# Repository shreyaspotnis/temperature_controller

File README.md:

# temperature_controller
A unipolar output temperature controller

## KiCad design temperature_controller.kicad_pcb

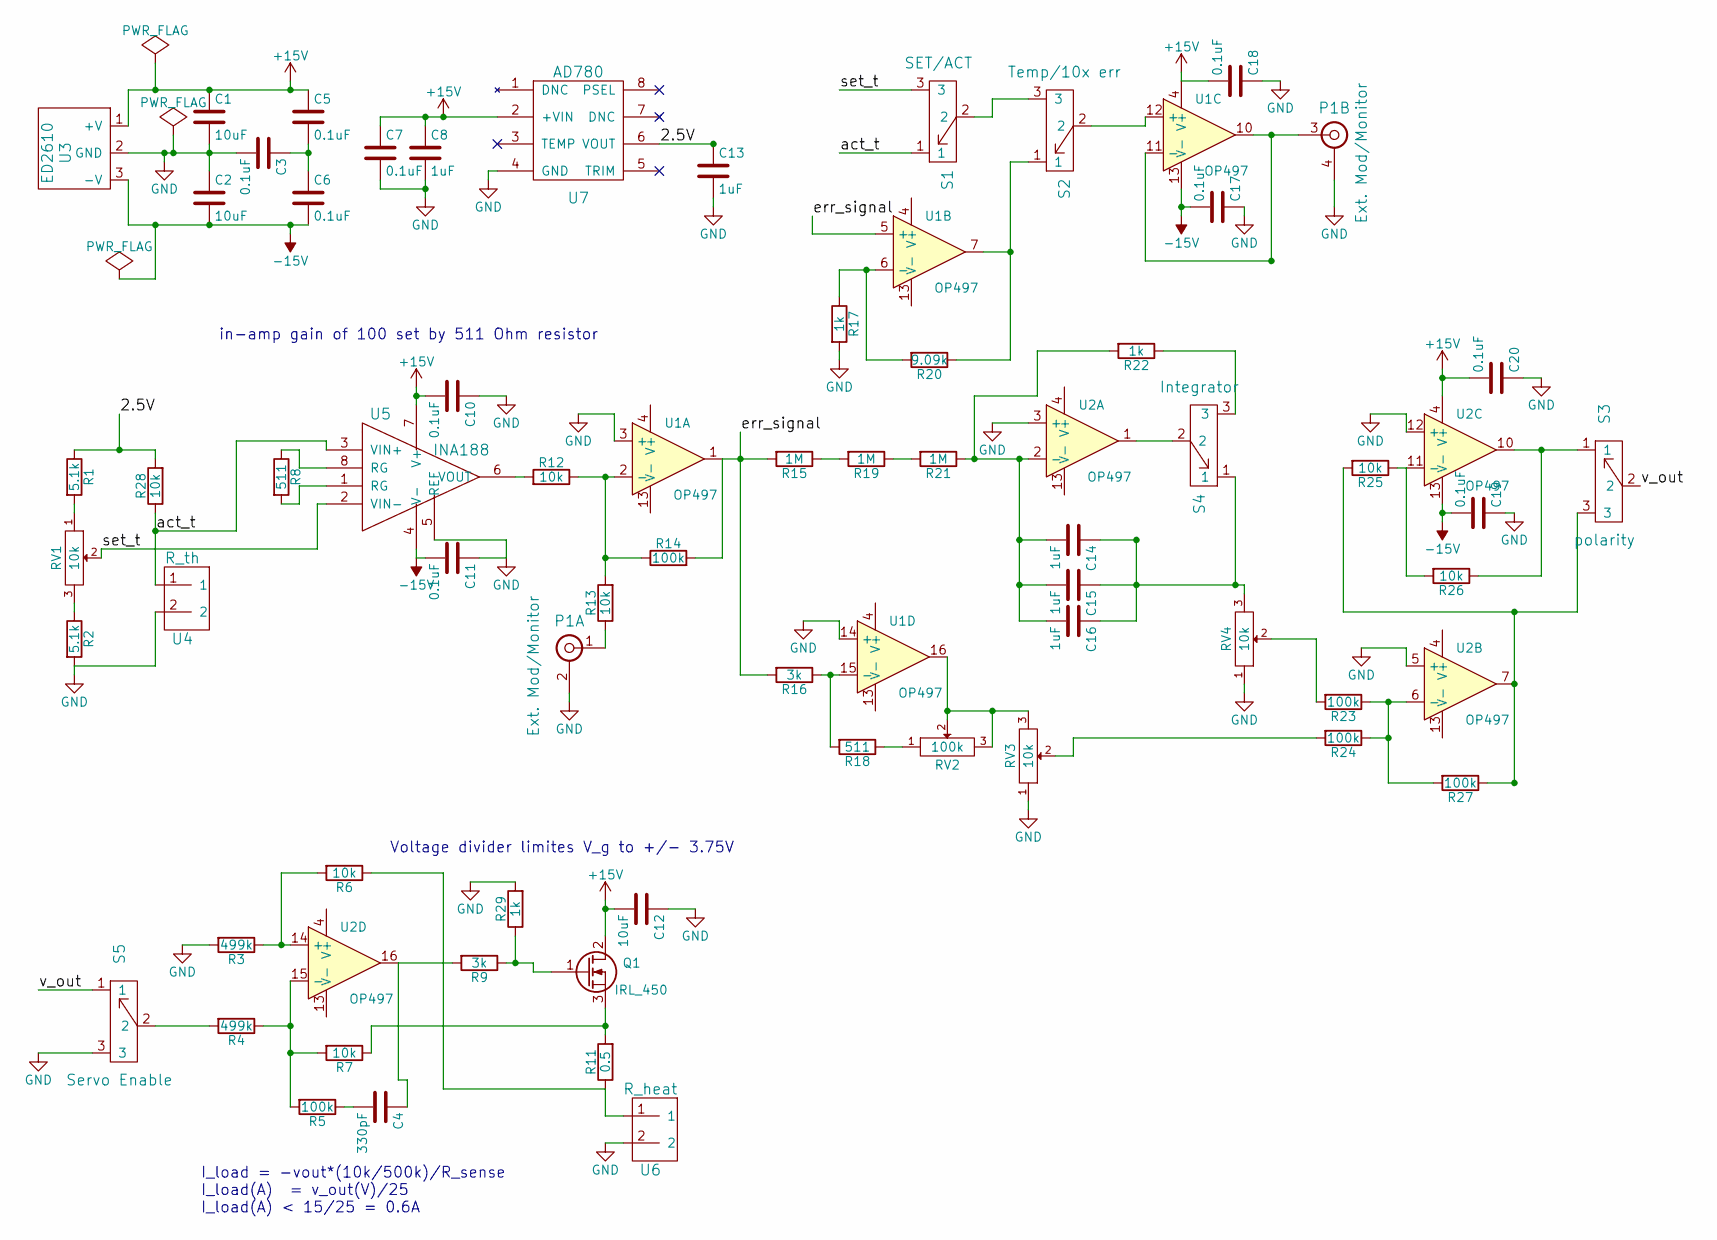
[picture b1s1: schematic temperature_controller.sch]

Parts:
C1, C2, C12: 10uF; C_0805_HandSoldering
C3, C5, C6, C7, C10, C11, C17, C18, C19, C20: 0.1uF; C_0805_HandSoldering
C4: 330pF; C_0603_HandSoldering
C8, C13, C14, C15, C16: 1uF; C_0603_HandSoldering
P1: Ext. Mod/Monitor; Dual-BNC-ARF2136
Q1: IRL_450; TO-220_Neutral123_Vertical
R1, R2: 5.1k; R_0603_HandSoldering
R3, R4: 499k; R_0603_HandSoldering
R5, R14, R23, R24, R27: 100k; R_0603_HandSoldering
R6, R7, R12, R13, R25, R26, R28: 10k; R_0603_HandSoldering
R8, R18: 511; R_0603_HandSoldering
R9: 3k; C_0603_HandSoldering
R11: 0.5; R_2512_HandSoldering
R15, R19, R21: 1M; R_0603_HandSoldering
R16: 3k; R_0603_HandSoldering
R17, R22, R29: 1k; R_0603_HandSoldering
R20: 9.09k; R_0603_HandSoldering
RV1: 10k; VishaySpectrol536
RV2: 100k; Bourns-PV36W104C01B00-trimmer
RV3, RV4: 10k; Bourns-PV36W104C01B00-trimmer
S1: SET/ACT; SPDT-Horizontal
S2: Temp/10x err; SPDT-Horizontal
S3: polarity; CJS-1200TB-SPDT
S4: Integrator; CJS-1200TB-SPDT
S5: Servo Enable; SPDT-Horizontal
U1, U2: OP497; SOIC-16W_7.5x10.3mm_Pitch1.27mm
U3: ED2610
U4: R_th; ED2580
U5: INA188; SOIC-8_3.9x4.9mm_Pitch1.27mm
U6: R_heat; ED2580
U7: AD780; SOIC-8_3.9x4.9mm_Pitch1.27mm

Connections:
+15V: C1.1, C5.1, C7.1, C8.1, C10.2, C12.2, C18.2, C20.2, Q1.2 (D), U1.4 (V+), U2.4 (V+), U3.1 (+V), U5.7 (V+), U7.2 (+VIN)
-15V: C2.2, C6.2, C11.2, C17.2, C19.2, U1.13 (V-), U2.13 (V-), U3.3 (-V), U5.4 (V-)
/2.5V: C13.1, R1.1, R28.2, U7.6 (VOUT)
/act_t: R28.1, S1.1, U4.1, U5.3 (VIN+)
/err_signal: R14.2, R15.2, R16.2, U1.1, U1.5 (+)
/set_t: RV1.2, S1.3, U5.2 (VIN-)
/v_out: S3.2, S5.1
GND: C1.2, C2.1, C3.2, C7.2, C8.2, C10.1, C11.1, C12.1, C13.2, C17.1, C18.1, C19.1, C20.1, P1.2, P1.4, R2.2, R3.2, R17.2, R29.2, RV3.1, RV4.1, S5.3, U1.3 (+), U1.14 (+), U2.3 (+), U2.5 (+), U2.12 (+), U3.2 (GND), U4.2, U5.5 (REF), U6.2, U7.4 (GND)
unnamed: C3.1, C5.2, C6.1
unnamed: C4.1, R9.2, U2.16
unnamed: C4.2, R5.1
unnamed: C14.1, C15.1, C16.1, RV4.3, S4.1
unnamed: C14.2, C15.2, C16.2, R21.1, R22.2, U2.2 (-)
unnamed: P1.1, R13.1
unnamed: P1.3, U1.10, U1.11 (-)
unnamed: Q1.1 (G), R9.1, R29.1
unnamed: Q1.3 (S), R7.1, R11.2
unnamed: R1.2, RV1.1
unnamed: R2.1, RV1.3
unnamed: R3.1, R6.2, U2.14 (+)
unnamed: R4.1, R5.2, R7.2, U2.15 (-)
unnamed: R4.2, S5.2
unnamed: R8.1, U5.8 (RG)
unnamed: R8.2, U5.1 (RG)
unnamed: R6.1, R11.1, U6.1
unnamed: R12.1, R13.2, R14.1, U1.2 (-)
unnamed: R12.2, U5.6 (VOUT)
unnamed: R15.1, R19.2
unnamed: R16.1, R18.2, U1.15 (-)
unnamed: R17.1, R20.2, U1.6 (-)
unnamed: R18.1, RV2.1
unnamed: R19.1, R21.2
unnamed: R20.1, S2.1, U1.7
unnamed: R22.1, S4.3
unnamed: R23.1, R24.1, R27.2, U2.6 (-)
unnamed: R23.2, RV4.2
unnamed: R24.2, RV3.2
unnamed: R25.1, R26.2, U2.11 (-)
unnamed: R25.2, R27.1, S3.3, U2.7
unnamed: R26.1, S3.1, U2.10
unnamed: RV2.2, RV2.3, RV3.3, U1.16
unnamed: S1.2, S2.3
unnamed: S2.2, U1.12 (+)
unnamed: S4.2, U2.1

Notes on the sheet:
in-amp gain of 100 set by 511 Ohm resistor
I_load = -vout*(10k/500k)/R_sense I_load(A) = v_out(V)/25 I_load(A) < 15/25 = 0.6A
Voltage divider limites V_g to +/- 3.75V

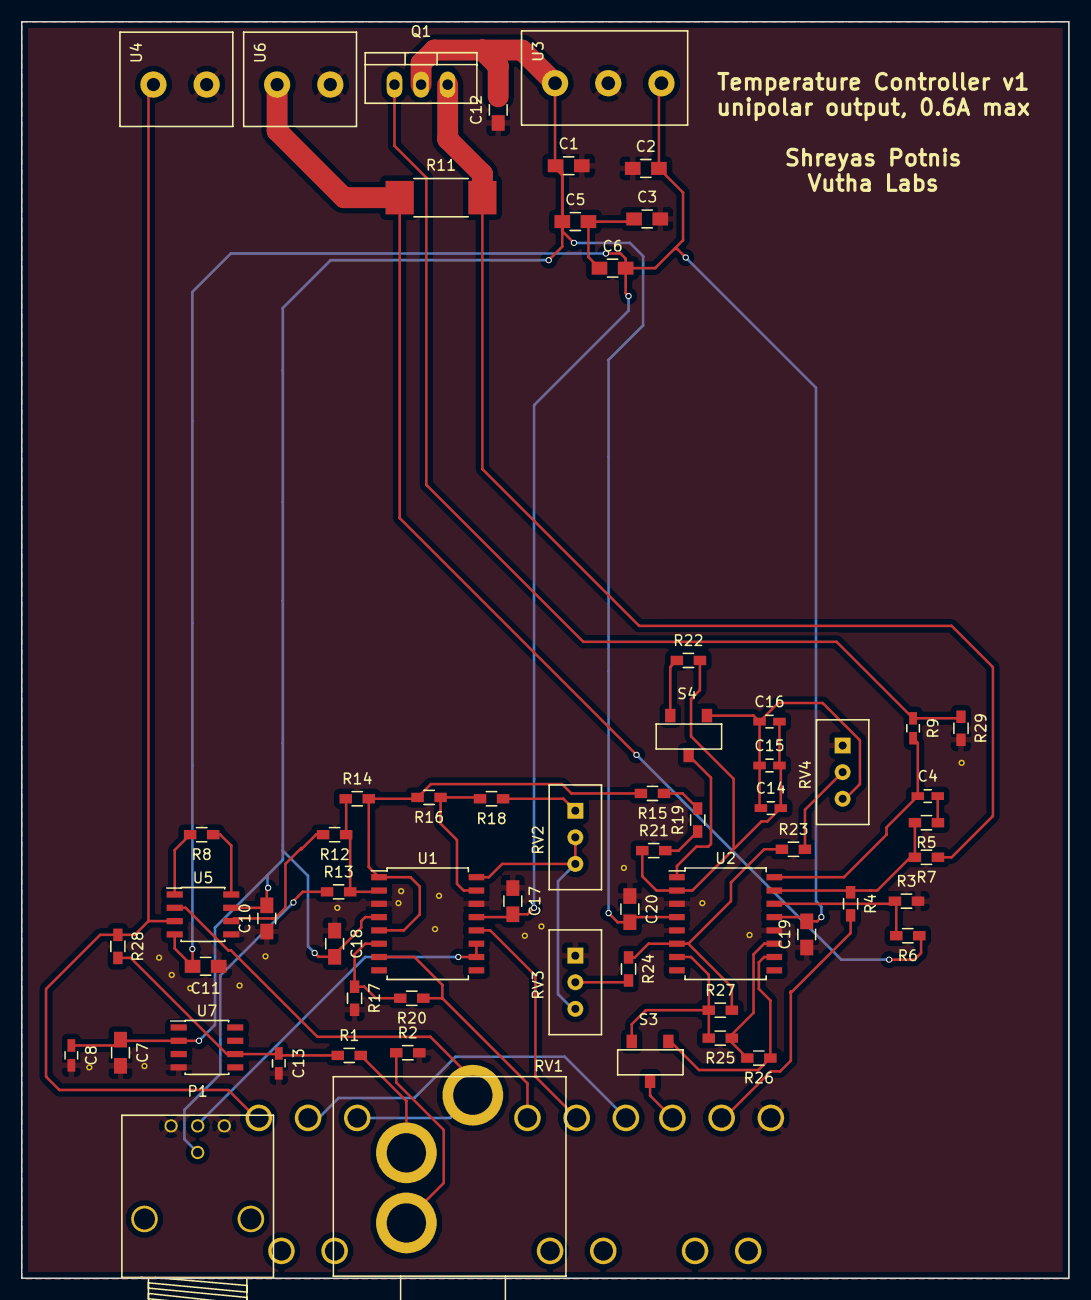
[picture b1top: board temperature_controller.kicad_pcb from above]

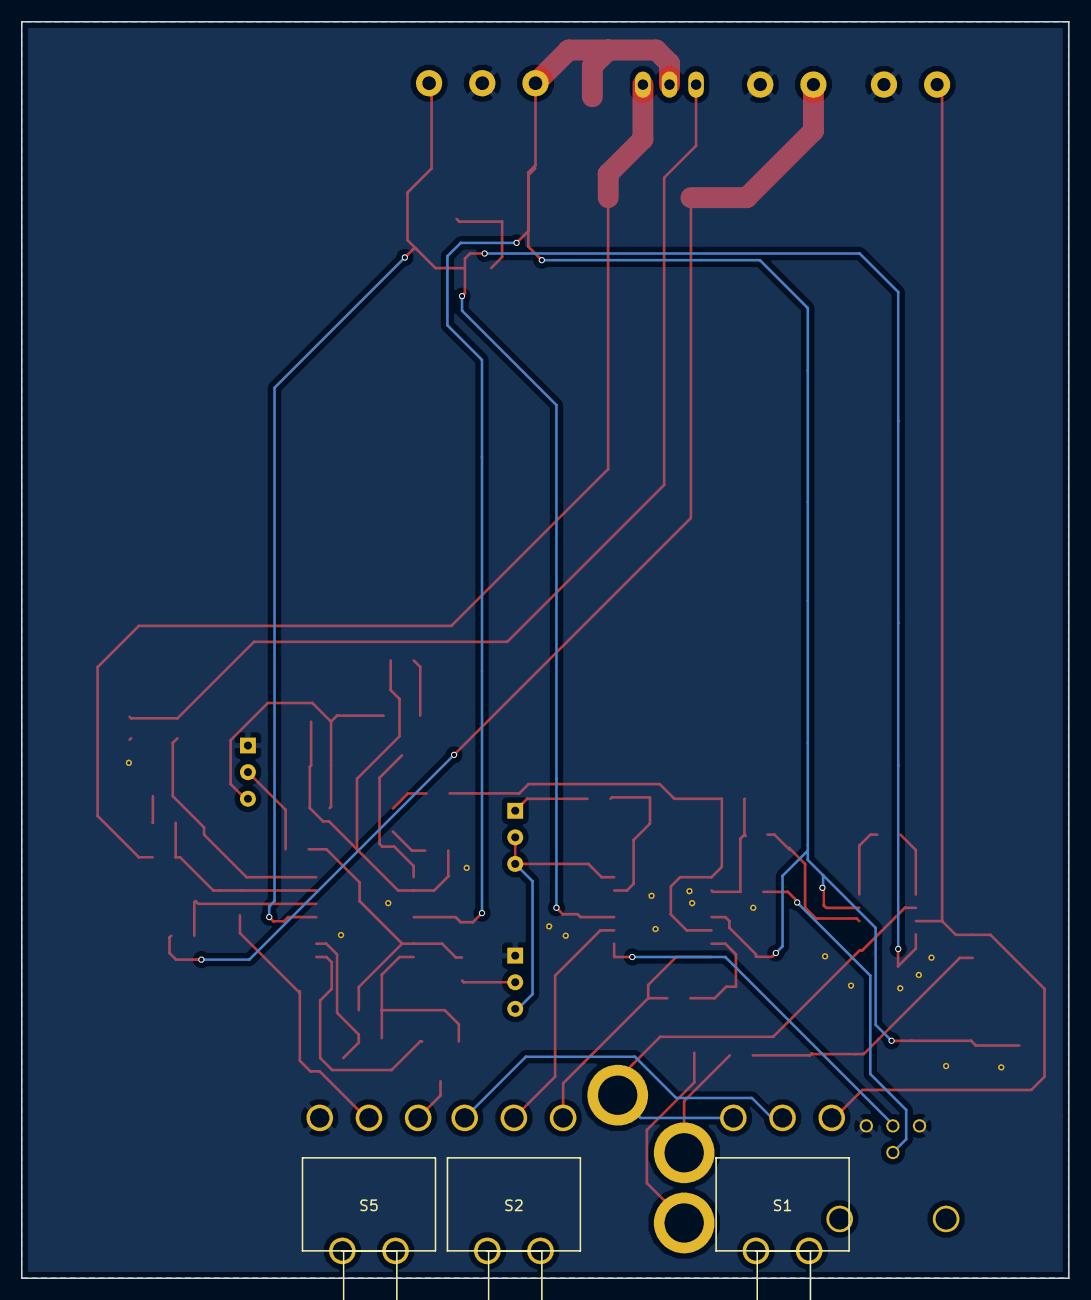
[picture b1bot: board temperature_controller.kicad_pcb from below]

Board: 2 copper layers, 100.0 x 120.0 mm, 65 parts (3 on the bottom side), 44 nets.

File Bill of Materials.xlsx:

Description | Digikey Part Number | Quantity | Footprint | Link | Parts
Resistors
10k Low Tempco Resistor | TNPU10.0KBACT-ND | 1.0 | "0603" | http://www.digikey.ca/product-detail/en/vishay-dale/TNPU0603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 | R28
10k resistor, 1% | 311-10.0KHRCT-ND | 7.0 | "0603" | http://www.digikey.ca/product-detail/en/yageo/RC0603FR-0710K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 | R13,R6,R7,R12,R14,R25,R26,
5.1k Low Tempco Resistor | RG16N5.1KWCT-ND | 2.0 | "0603" | http://www.digikey.ca/product-detail/en/susumu/RG1608N-512-W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 | R1,R2
499k | 311-499KHRCT-ND | 2.0 | "0603" | http://www.digikey.ca/product-detail/en/yageo/RC0603FR-07499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 | R3,R4
100k | 311-100KHRCT-ND | 4.0 | "0603" | http://www.digikey.ca/product-detail/en/yageo/RC0603FR-07100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 | R5,R23,R24,R27
1M | 311-1.00MHRCT-ND | 3.0 | "0603" | http://www.digikey.ca/product-detail/en/yageo/RC0603FR-071ML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 | R15,R19,R21
3k | 311-3.0KGRCT-ND | 1.0 | "0603" | http://www.digikey.ca/product-detail/en/yageo/RC0603JR-073KL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 | R9, R16
1k | 311-1.0KGRCT-ND | 3.0 | "0603" | http://www.digikey.ca/product-search/en?keywords=311-1.0KGRCT-ND | R17,R22,R29
511Ohm | 311-511HRTR-ND | 2.0 | "0603" | http://www.digikey.ca/product-detail/en/yageo/RC0603FR-07511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 | R8,R18
9.09k | 311-9.09KHRCT-ND | 1.0 | "0603" | http://www.digikey.ca/product-detail/en/yageo/RC0603FR-079K0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 | R20
0.5 Ohm Sense resistor | CSRN2512FKR500CT-ND | 1.0 | "2512" | http://www.digikey.ca/product-detail/en/stackpole-electronic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 | R11
ICs
2.5V Reference | AD780ARZ-ND | 1.0 | 8-SOIC | http://www.digikey.ca/product-detail/en/analog-devices-inc/A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 | U7
OP497 quad opamp picometer | OP497GSZ-ND | 2.0 | 16-SOIC | http://www.digikey.ca/product-detail/en/analog-devices-inc/O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 | U1,U2
INA188 in-amp zero drift | 296-43151-1-ND | 1.0 | 8-SOIC | http://www.digikey.ca/product-detail/en/texas-instruments/IN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 | U5
IRL540 | IRL540PBF-ND | 1.0 | TO220 | http://www.digikey.ca/product-detail/en/vishay-siliconix/IRL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 | Q1
Connectors
Dual-BNC connector | ARF2136-ND | 1.0 | Custom | http://www.digikey.ca/product-detail/en/amphenol-rf-division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 | P1
3 pin wire to board | ED2610-ND | 1.0 | Custom | http://www.digikey.ca/product-detail/en/on-shore-technology-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 | U3
2 pin wire to board | ED2580-ND | 2.0 | Custom | http://www.digikey.ca/product-detail/en/on-shore-technology-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 | U4, U6
Capacitors
0.1uF | 445-2514-1-ND | 10.0 | "0805" | http://www.digikey.ca/product-detail/en/tdk-corporation/C201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 | C3,C5,C6,C7,C10,C11,C17,C18,C19,C20
1uF | 311-1372-1-ND | 5.0 | "0603" | http://www.digikey.ca/product-detail/en/yageo/CC0603ZRY5V7BB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 | C8,C13,C14,C15,C16
10uF | 490-6473-1-ND | 3.0 | "0805" | http://www.digikey.ca/product-detail/en/murata-electronics-n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 | C1,C2,C12
330pF | 1276-1787-1-ND | 1.0 | "0603" | http://www.digikey.ca/product-detail/en/samsung-electro-mech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 | C4
Trimpots
100k | 490-2876-ND | 1.0 | Custom | http://www.digikey.ca/product-detail/en/bourns-inc/PV36W104C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 | RV2
10k | 490-2875-ND | 2.0 | Custom | http://www.digikey.ca/products/en?keywords=PV36W103C01B00 | RV3,RV4
Others
10k 10 turn, Vishay spectrol | 534B1103JC-ND | 1.0 | Custom | http://www.digikey.ca/product-detail/en/vishay-spectrol/534B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 | RV1
Throughhole right angle toggle switch | EG2362-ND | 3.0 | Custom | http://www.digikey.ca/product-search/en?keywords=100SP1T2B4M6QE | S1, S2, S5
DIP Switch SDPT | 563-1022-2-ND | 2.0 | Custom | http://www.digikey.ca/product-detail/en/copal-electronics-in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 | S3, S4
Enclosure
Box, Aluminum 4.724" L x 4.055" W (119.99mm x 103.00mm) X 2.087" (53.00mm) | HM974-ND | 1.0 |  | http://www.digikey.ca/product-detail/en/hammond-manufacturin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

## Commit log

2017-01-06 :lollipop: Added .gitattributes & .gitignore files
2017-01-06 Design almost finished
2017-04-05 final design
2017-04-05 Added bill of materials
